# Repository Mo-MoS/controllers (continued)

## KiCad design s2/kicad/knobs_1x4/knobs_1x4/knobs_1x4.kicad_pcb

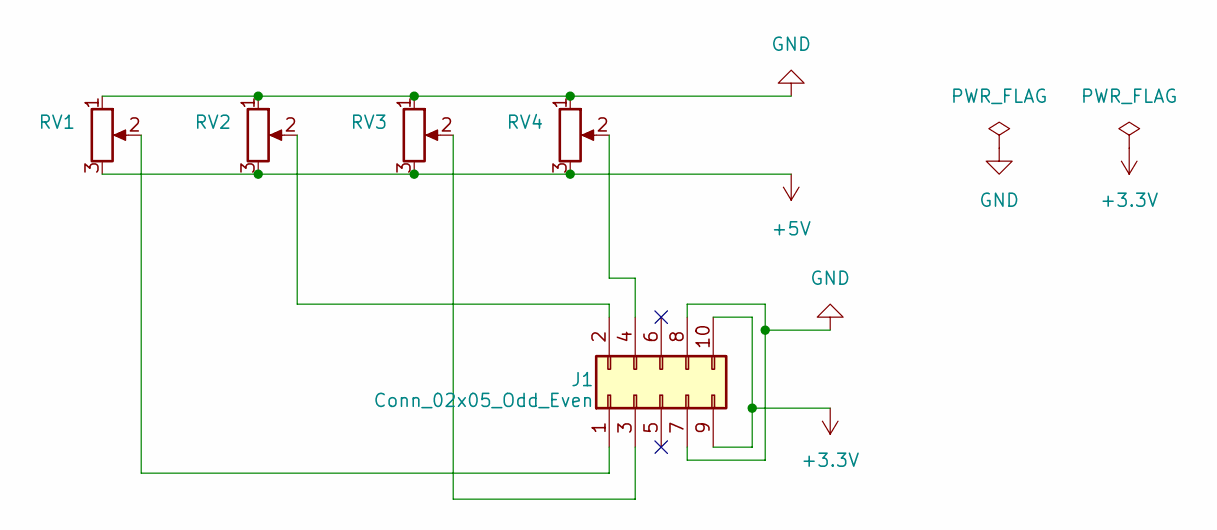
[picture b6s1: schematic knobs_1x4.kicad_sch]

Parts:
J1: Conn_02x05_Odd_Even; PinHeader_2x05_P2.54mm_Horizontal
RV1, RV2, RV3, RV4: R_Potentiometer; Potentiometer_RV09

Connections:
+3.3V: J1.9, J1.10
+5V: RV1.3, RV2.3, RV3.3, RV4.3
GND: J1.7, J1.8, RV1.1, RV2.1, RV3.1, RV4.1
unnamed: J1.1, RV1.2
unnamed: J1.2, RV2.2
unnamed: J1.3, RV3.2
unnamed: J1.4, RV4.2

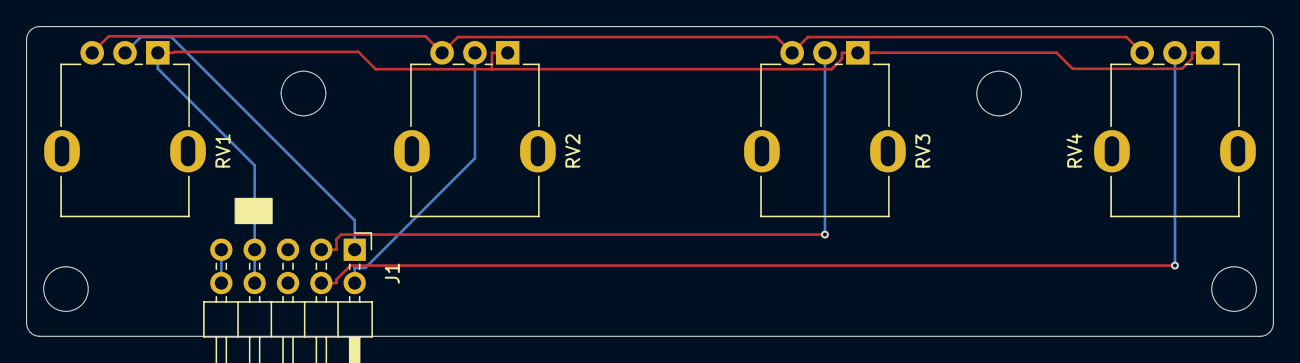
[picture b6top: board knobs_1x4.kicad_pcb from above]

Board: 2 copper layers, 95.0 x 23.6 mm, 5 parts (0 on the bottom side), 7 nets.

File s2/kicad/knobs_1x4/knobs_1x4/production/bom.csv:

Designator,Footprint,Quantity,Value,LCSC Part #
J1,PinHeader_2x05_P2.54mm_Horizontal,1,Conn_02x05_Odd_Even,
"RV1, RV2, RV3, RV4",Potentiometer_RV09,4,R_Potentiometer,

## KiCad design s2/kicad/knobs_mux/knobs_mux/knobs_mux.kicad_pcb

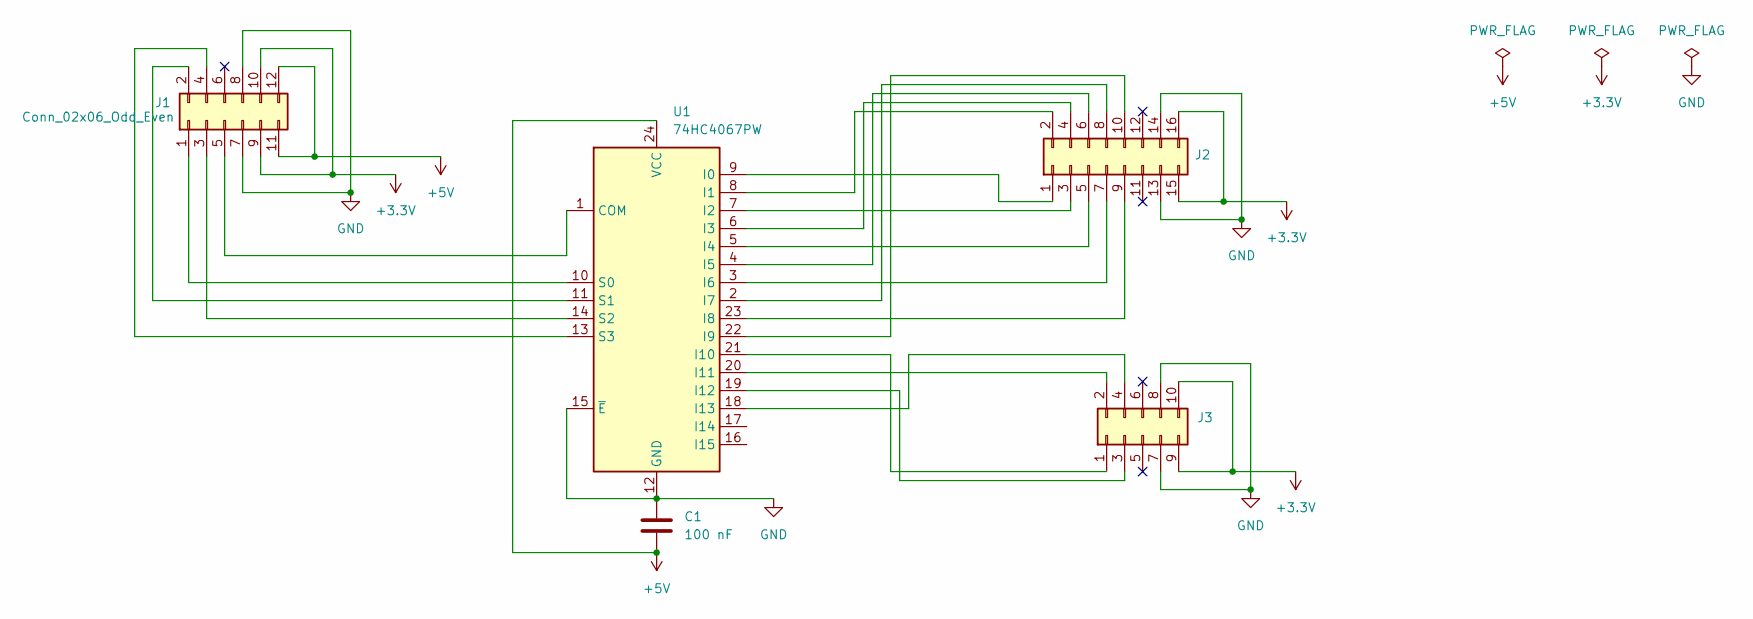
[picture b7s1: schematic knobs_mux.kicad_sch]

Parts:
C1: 100 nF; C_0402_1005Metric
J1: Conn_02x06_Odd_Even; PinHeader_2x06_P2.54mm_Horizontal
J2: Conn_02x08_Odd_Even; PinSocket_2x08_P2.54mm_Horizontal
J3: Conn_02x05_Odd_Even; PinSocket_2x05_P2.54mm_Horizontal
U1: 74HC4067PW; SOP-24_7.5x15.4mm_P1.27mm

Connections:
+3.3V: J1.9, J1.10, J2.15, J2.16, J3.9, J3.10
+5V: C1.2, J1.11, J1.12, U1.24 (VCC)
GND: C1.1, J1.7, J1.8, J2.13, J2.14, J3.7, J3.8, U1.12 (GND), U1.15 (~E)
unnamed: J1.1, U1.10 (S0)
unnamed: J1.2, U1.11 (S1)
unnamed: J1.3, U1.14 (S2)
unnamed: J1.4, U1.13 (S3)
unnamed: J1.5, U1.1 (COM)
unnamed: J2.1, U1.9 (I0)
unnamed: J2.2, U1.8 (I1)
unnamed: J2.3, U1.7 (I2)
unnamed: J2.4, U1.6 (I3)
unnamed: J2.5, U1.5 (I4)
unnamed: J2.6, U1.4 (I5)
unnamed: J2.7, U1.3 (I6)
unnamed: J2.8, U1.2 (I7)
unnamed: J2.9, U1.23 (I8)
unnamed: J2.10, U1.22 (I9)
unnamed: J3.1, U1.21 (I10)
unnamed: J3.2, U1.20 (I11)
unnamed: J3.3, U1.19 (I12)
unnamed: J3.4, U1.18 (I13)

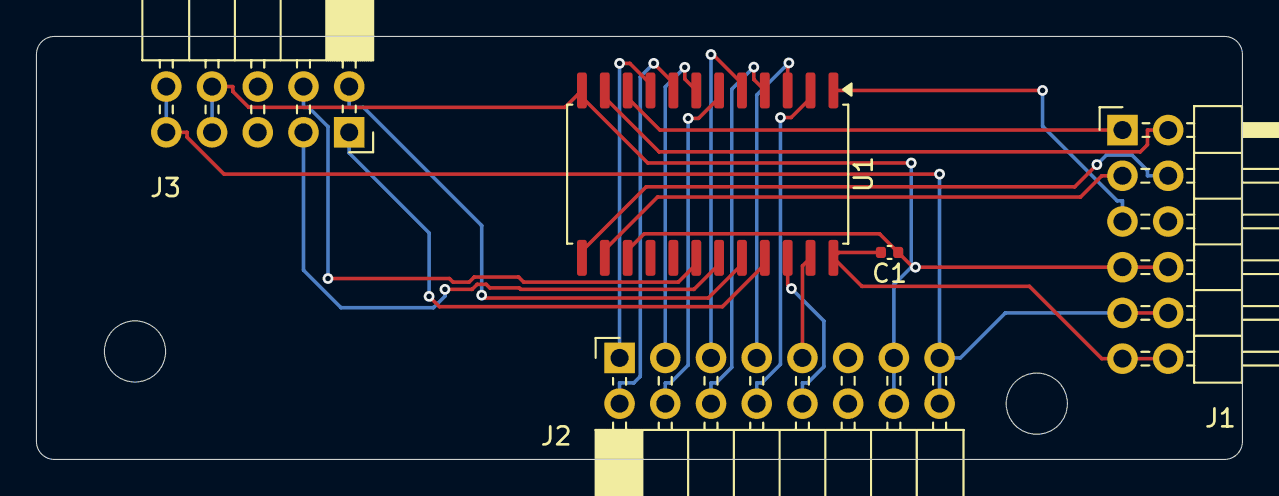
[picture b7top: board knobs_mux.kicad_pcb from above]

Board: 2 copper layers, 67.0 x 23.5 mm, 5 parts (0 on the bottom side), 22 nets.

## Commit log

2025-09-30 init readme
2025-10-04 pcb order update
2025-10-12 added kicad projects
2025-10-12 readme rework
2025-10-12 readme update
2025-10-17 added pcbs
2025-10-19 sunday update
2025-10-19 frontplate svg
2025-10-24 S2 OSC pics
2025-10-25 added s2-osc front eurorack
2025-10-28 added knobs_7_mux
2025-10-29 added enc_single_filter
